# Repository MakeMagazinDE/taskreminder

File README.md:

Maker Media GmbH
*** 

# Task-Reminder

### Aufgaben, die man nicht im Blick hat, können schnell mal unter den Tisch fallen. Den Task-Reminder mit seinen LEDs kann man jedoch kaum übersehen. Er weiß genau, welche Aufgabe als Nächstes ansteht und leuchtet unermüdlich, bis man sie erledigt hat.

Ergänzend zum Artikel aus der Make 1/24 findest du hier die benötigten MicroPython-Programme für den ESP32, die Formeln für das Google-Sheet sowie die CAD-Daten für die Platine und das Gehäuse des Task-Reminders.

Den Artikel mit der Bauanleitung gibt es in der **[Make-Ausgabe 1/24](https://www.heise.de/select/make/2024/1)** zu lesen.

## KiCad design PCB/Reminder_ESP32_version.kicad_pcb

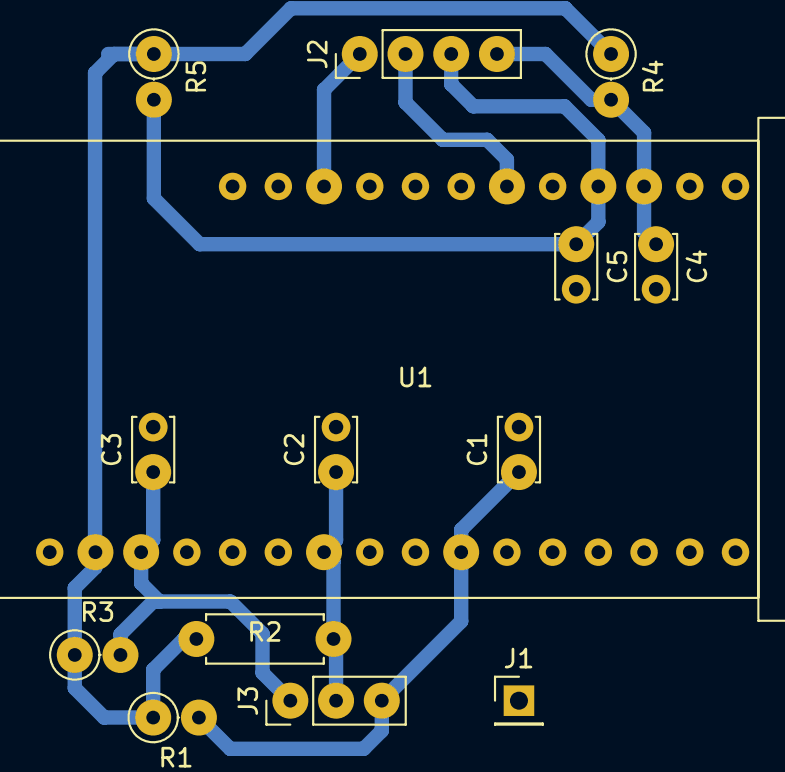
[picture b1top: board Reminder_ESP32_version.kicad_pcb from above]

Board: 2 copper layers, 14 parts (0 on the bottom side), 9 nets.

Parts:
C1, C2, C3, C4, C5: 100nF; C_Disc_D3.4mm_W2.1mm_P2.50mm
J1: Conn_01x01_Female; PinHeader_1x01_P2.54mm_Vertical
J2: Conn_01x04_Female; PinHeader_1x04_P2.54mm_Vertical
J3: Conn_01x03_Female; PinHeader_1x03_P2.54mm_Vertical
R1, R3, R4, R5: 1k; R_Axial_DIN0207_L6.3mm_D2.5mm_P2.54mm_Vertical
R2: 1k; R_Axial_DIN0207_L6.3mm_D2.5mm_P7.62mm_Horizontal
U1: ESP32_ePulse_Feather; ESP32 ePulse Feather

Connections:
+3.3V: R1.1, R2.1, R3.1, R4.1, R5.1, U1.14 (3V3)
GND: C1.2, C2.2, C3.2, C4.2, C5.2, J1.1, U1.16 (GND)
unnamed: C3.1, J3.1, R3.2, U1.15 (02)
unnamed: C4.1, J2.4, R4.2, U1.3 (14_CLK)
unnamed: C5.1, J2.3, R5.2, U1.4 (32)
unnamed: J2.1, U1.10 (USB)
unnamed: J2.2, U1.6 (33)
unnamed: C2.1, J3.2, R2.2, U1.19 (34)
unnamed: C1.1, J3.3, R1.2, U1.22 (04)

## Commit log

2024-01-26 Create empty
